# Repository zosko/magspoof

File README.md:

# Magspoof with Arduino Nano
Arduino magnetic card emulator track 1 and track 2

Components:
- L293D
- Arduino Nano
- COIL from 24awg wire, ~50 turns on 3cm diametar

Original: https://github.com/samyk/magspoof

## PCB Design

**Huge thanks to [PCBWay](https://pcbway.com) for sponsoring this project!**

PCBWay is a leading provider of high-quality printed circuit boards (PCBs), offering reliable and affordable solutions for both hobbyists and professionals. Their services include rapid prototyping, PCB assembly, instant online quotations, expert design verification, and a streamlined ordering experience.

Their comprehensive range of services includes:
- PCB prototyping
- Assembly services
- Instant online quotations
- Expert design verification
- A streamlined, user-friendly ordering system

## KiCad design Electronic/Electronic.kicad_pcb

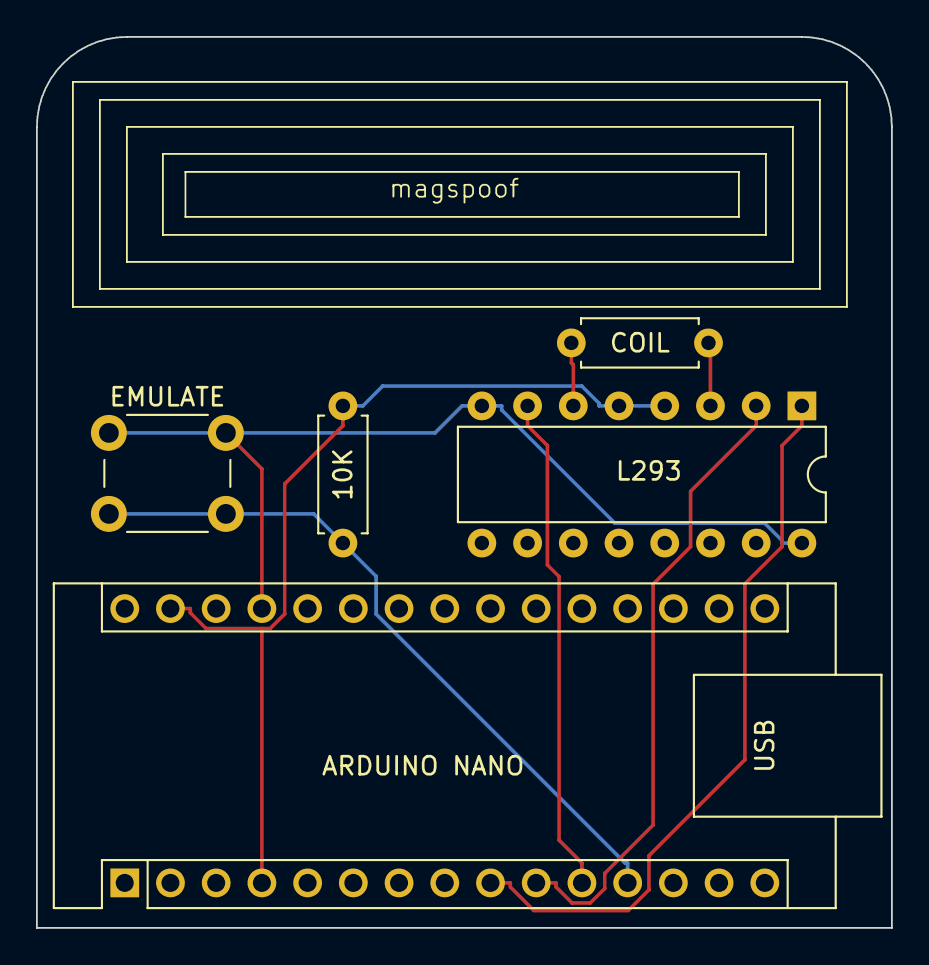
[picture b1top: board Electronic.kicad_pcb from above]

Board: 2 copper layers, 47.5 x 49.5 mm, 5 parts (0 on the bottom side), 8 nets.

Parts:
10K: 10K; R_Axial_DIN0207_L6.3mm_D2.5mm_P7.62mm_Horizontal
ARDUINO NANO: Arduino_Nano_v3.x; Arduino_Nano
COIL: L; R_Axial_DIN0207_L6.3mm_D2.5mm_P7.62mm_Horizontal
EMULATE: SW_Push; SW_PUSH_6mm
L293: L293D; DIP-16_W7.62mm

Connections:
COIL_A: COIL.1, L293.3 (1Y)
COIL_B: COIL.2, L293.6 (2Y)
GND: 10K.2, ARDUINO NANO.4 (GND), ARDUINO NANO.29 (GND), L293.4 (GND), L293.5 (GND)
PIN_A: ARDUINO NANO.10 (D7), L293.2 (1A)
PIN_B: ARDUINO NANO.11 (D8), L293.7 (2A)
PIN_BUTTON: 10K.1, ARDUINO NANO.12 (D9), EMULATE.2
PIN_ENABLE: ARDUINO NANO.9 (D6), L293.1 (EN1,2)
VCC: ARDUINO NANO.27 (+5V), EMULATE.1, L293.8 (VCC2), L293.16 (VCC1)

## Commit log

2024-12-18 update project
